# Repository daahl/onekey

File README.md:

# Just another OneKey keyboard

Ever felt the need for having just one more key to you keyboard? Well here you go.

Uses an ATTiny85 for the USB interface.

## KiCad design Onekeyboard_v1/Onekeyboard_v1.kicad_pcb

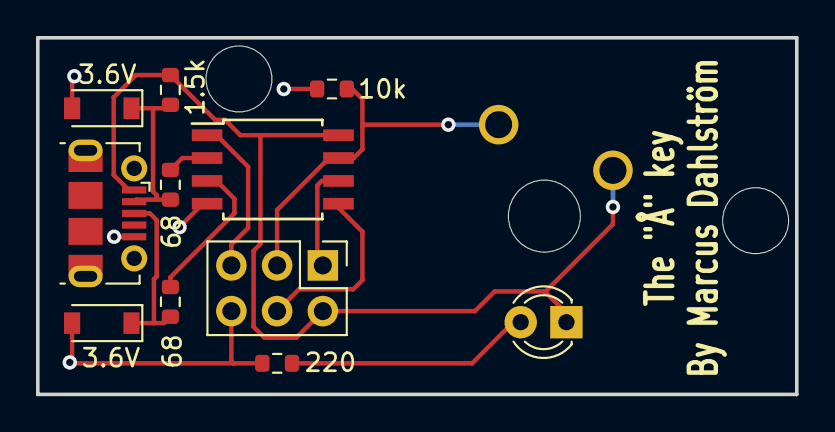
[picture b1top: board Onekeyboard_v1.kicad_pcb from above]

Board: 2 copper layers, 42.2 x 19.8 mm, 12 parts (1 on the bottom side), 11 nets.

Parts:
1.5k, 10k, 68, 68#2, 220: R_Small; R_0603_1608Metric
3.6V, 3.6V#2: D_Zener; D_SOD-123
D1: LED; LED_D3.0mm
J1: USB_B_Micro; USB_Micro-B_Molex-105017-0001
J2: Conn_02x03_Odd_Even; PinHeader_2x03_P2.54mm_Vertical
SW1: SW_Push; SW_Cherry_MX_1.00u_Plate
U1: ATtiny85-20SU; SOIJ-8_5.3x5.3mm_P1.27mm

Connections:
GND: 3.6V.2, 3.6V#2.2, 10k.1, 220.2, J1.5, J2.6, U1.4
MISO: J2.1, U1.6
MOSI: J2.4, U1.5
unnamed: 1.5k.2, 3.6V#2.1, 68.1, J1.2
unnamed: 3.6V.1, 68#2.1, J1.3
unnamed: 68.2, U1.2
unnamed: 68#2.2, U1.3
unnamed: 220.1, D1.2
RESET: J2.5, U1.1
SCK: 10k.2, J2.3, SW1.1, U1.7
VCC: 1.5k.1, D1.1, J1.1, J2.2, SW1.2, U1.8
